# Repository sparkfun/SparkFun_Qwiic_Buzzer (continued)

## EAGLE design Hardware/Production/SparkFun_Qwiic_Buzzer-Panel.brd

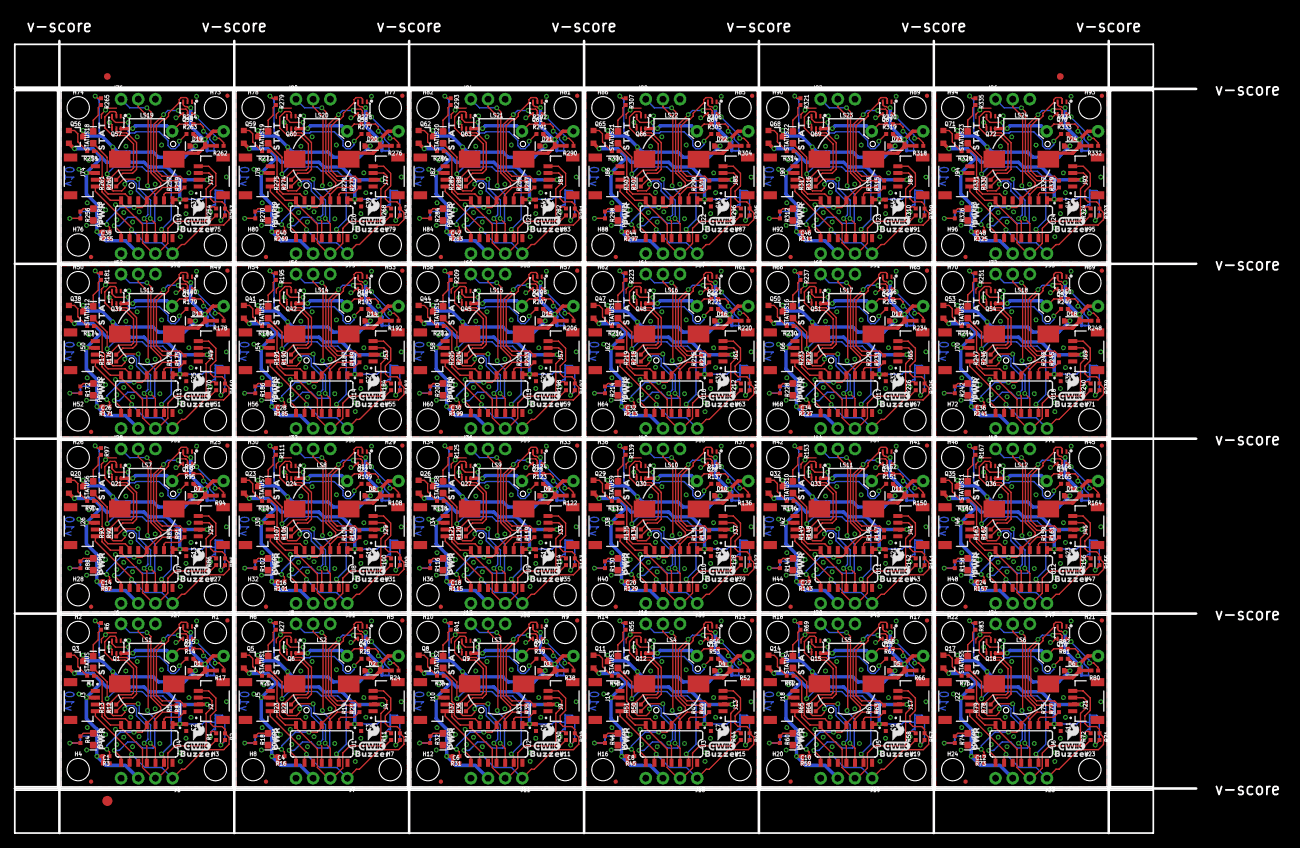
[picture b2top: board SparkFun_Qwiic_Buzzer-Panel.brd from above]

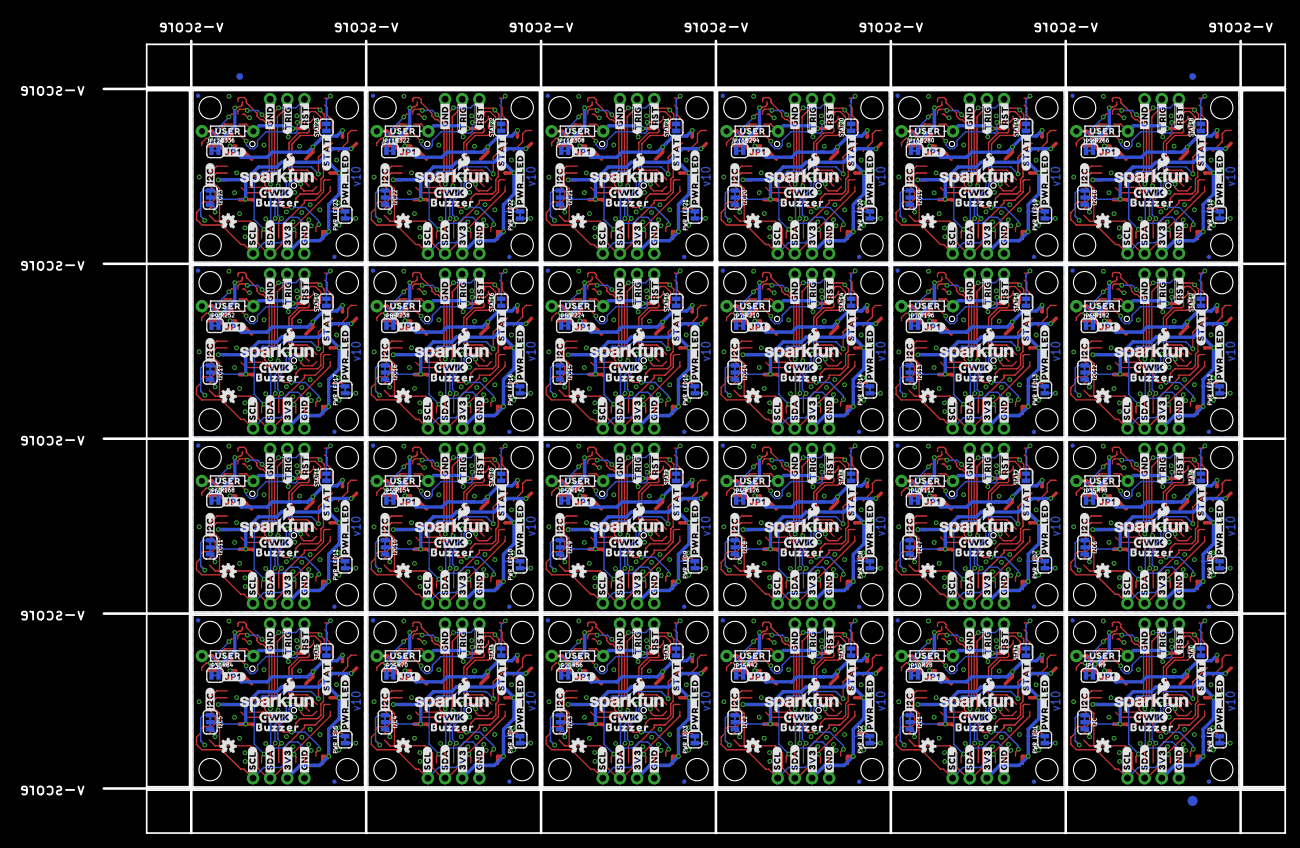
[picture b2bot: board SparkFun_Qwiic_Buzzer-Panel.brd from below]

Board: 2 copper layers, 175.0 x 117.3 mm, 1470 parts (555 on the bottom side), 696 nets.

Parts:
C1, C4, C6, C8, C10, C12, C14, C16, C18, C20, C22, C24, C26, C28, C30, C32, C34, C36, C38, C40, C42, C44, C46, C48: 10uF; 0402-TIGHT
C2, C3, C5, C7, C9, C11, C13, C15, C17, C19, C21, C23, C25, C27, C29, C31, C33, C35, C37, C39, C41, C43, C45, C47: 0.1uF; 0402-TIGHT
D1, D2, D3, D4, D5, D6, D7, D8, D9, D10, D11, D12, D13, D14, D15, D16, D17, D18, D19, D20, D21, D22, D23, D24: 0.5A/40V/420mV; SOD-323
E$1, E$2, E$3, E$4: FIDUCIAL-1X2
E$5, E$6: FIDUCIAL-1.5X3
H1, H2, H3, H4, H5, H6, H7, H8, H9, H10, H11, H12, H13, H14, H15, H16, H17, H18, H19, H20, H21, H22, H23, H24, H25, H26, H27, H28, H29, H30, H31, H32, H33, H34, H35, H36, H37, H38, H39, H40, H41, H42, H43, H44, H45, H46, H47, H48, H49, H50, H51, H52, H53, H54, H55, H56, H57, H58, H59, H60, H61, H62, H63, H64, H65, H66, H67, H68, H69, H70, H71, H72, H73, H74, H75, H76, H77, H78, H79, H80, H81, H82, H83, H84, H85, H86, H87, H88, H89, H90, H91, H92, H93, H94, H95, H96: STAND-OFF
I2C, I2C1, I2C2, I2C3, I2C4, I2C5, I2C6, I2C7, I2C8, I2C9, I2C10, I2C11, I2C12, I2C13, I2C14, I2C15, I2C16, I2C17, I2C18, I2C19, I2C20, I2C21, I2C22, I2C23: JUMPER-SMT_3_2-NC_TRACE_SILK; SMT-JUMPER_3_2-NC_TRACE_SILK
J1, J7, J11, J15, J19, J23, J27, J31, J35, J39, J43, J47, J51, J55, J59, J63, J67, J71, J75, J79, J83, J87, J91, J95: 1X04_NO_SILK
J2, J3, J4, J5, J9, J10, J13, J14, J17, J18, J21, J22, J25, J26, J29, J30, J33, J34, J37, J38, J41, J42, J45, J46, J49, J50, J53, J54, J57, J58, J61, J62, J65, J66, J69, J70, J73, J74, J77, J78, J81, J82, J85, J86, J89, J90, J93, J94: QWIIC_RA; JST04_1MM_RA
J6, J8, J12, J16, J20, J24, J28, J32, J36, J40, J44, J48, J52, J56, J60, J64, J68, J72, J76, J80, J84, J88, J92, J96: 1X03_NO_SILK
JP1, JP10, JP15, JP20, JP25, JP30, JP35, JP40, JP45, JP50, JP55, JP60, JP65, JP70, JP75, JP80, JP85, JP90, JP95, JP100, JP105, JP110, JP115, JP120: SMT-JUMPER_2_NC_TRACE_SILK
JP2, JP3, JP4, JP5, JP6, JP7, JP8, JP9, JP11, JP12, JP13, JP14, JP16, JP17, JP18, JP19, JP21, JP22, JP23, JP24, JP26, JP27, JP28, JP29, JP31, JP32, JP33, JP34, JP36, JP37, JP38, JP39, JP41, JP42, JP43, JP44, JP46, JP47, JP48, JP49, JP51, JP52, JP53, JP54, JP56, JP57, JP58, JP59, JP61, JP62, JP63, JP64, JP66, JP67, JP68, JP69, JP71, JP72, JP73, JP74, JP76, JP77, JP78, JP79, JP81, JP82, JP83, JP84, JP86, JP87, JP88, JP89, JP91, JP92, JP93, JP94, JP96, JP97, JP98, JP99, JP101, JP102, JP103, JP104, JP106, JP107, JP108, JP109, JP111, JP112, JP113, JP114, JP116, JP117, JP118, JP119: FIDUCIALUFIDUCIAL; FIDUCIAL-MICRO
LOGO1, LOGO3, LOGO9, LOGO13, LOGO17, LOGO21, LOGO25, LOGO29, LOGO33, LOGO37, LOGO41, LOGO45, LOGO49, LOGO53, LOGO57, LOGO61, LOGO65, LOGO69, LOGO73, LOGO77, LOGO81, LOGO85, LOGO89, LOGO93: OSHW-LOGOMINI; OSHW-LOGO-MINI
LOGO2, LOGO7, LOGO11, LOGO15, LOGO19, LOGO23, LOGO27, LOGO31, LOGO35, LOGO39, LOGO43, LOGO47, LOGO51, LOGO55, LOGO59, LOGO63, LOGO67, LOGO71, LOGO75, LOGO79, LOGO83, LOGO87, LOGO91, LOGO95: SFE_LOGO_NAME_FLAME.1_INCH; SFE_LOGO_NAME_FLAME_.1
LOGO4, LOGO6, LOGO10, LOGO14, LOGO18, LOGO22, LOGO26, LOGO30, LOGO34, LOGO38, LOGO42, LOGO46, LOGO50, LOGO54, LOGO58, LOGO62, LOGO66, LOGO70, LOGO74, LOGO78, LOGO82, LOGO86, LOGO90, LOGO94: SFE_LOGO_FLAME.1_INCH; SFE_LOGO_FLAME_.1
LOGO5, LOGO8, LOGO12, LOGO16, LOGO20, LOGO24, LOGO28, LOGO32, LOGO36, LOGO40, LOGO44, LOGO48, LOGO52, LOGO56, LOGO60, LOGO64, LOGO68, LOGO72, LOGO76, LOGO80, LOGO84, LOGO88, LOGO92, LOGO96: QWIIC_LOGO_4MM; QWIIC_4MM
LS1, LS2, LS3, LS4, LS5, LS6, LS7, LS8, LS9, LS10, LS11, LS12, LS13, LS14, LS15, LS16, LS17, LS18, LS19, LS20, LS21, LS22, LS23, LS24: BUZZER; BUZZER-CCV
POWER, POWER1, POWER2, POWER3, POWER4, POWER5, POWER6, POWER7, POWER8, POWER9, POWER10, POWER11, POWER12, POWER13, POWER14, POWER15, POWER16, POWER17, POWER18, POWER19, POWER20, POWER21, POWER22, POWER23: Red; LED-0603
PWR_LED, PWR_LED1, PWR_LED2, PWR_LED3, PWR_LED4, PWR_LED5, PWR_LED6, PWR_LED7, PWR_LED8, PWR_LED9, PWR_LED10, PWR_LED11, PWR_LED12, PWR_LED13, PWR_LED14, PWR_LED15, PWR_LED16, PWR_LED17, PWR_LED18, PWR_LED19, PWR_LED20, PWR_LED21, PWR_LED22, PWR_LED23: PWR_LED; SMT-JUMPER_2_NC_TRACE_SILK
Q1, Q2, Q4, Q6, Q7, Q9, Q10, Q12, Q13, Q15, Q16, Q18, Q19, Q21, Q22, Q24, Q25, Q27, Q28, Q30, Q31, Q33, Q34, Q36, Q37, Q39, Q40, Q42, Q43, Q45, Q46, Q48, Q49, Q51, Q52, Q54, Q55, Q57, Q58, Q60, Q61, Q63, Q64, Q66, Q67, Q69, Q70, Q72: SC70-6
Q3, Q5, Q8, Q11, Q14, Q17, Q20, Q23, Q26, Q29, Q32, Q35, Q38, Q41, Q44, Q47, Q50, Q53, Q56, Q59, Q62, Q65, Q68, Q71: 200mA/40V; SOT23-3
R1, R2, R6, R10, R11, R15, R26, R27, R29, R30, R40, R41, R43, R44, R54, R55, R57, R58, R68, R69, R71, R72, R82, R83, R85, R86, R96, R97, R99, R100, R110, R111, R113, R114, R124, R125, R127, R128, R138, R139, R141, R142, R152, R153, R155, R156, R166, R167, R169, R170, R180, R181, R183, R184, R194, R195, R197, R198, R208, R209, R211, R212, R222, R223, R225, R226, R236, R237, R239, R240, R250, R251, R253, R254, R264, R265, R267, R268, R278, R279, R281, R282, R292, R293, R295, R296, R306, R307, R309, R310, R320, R321, R323, R324, R334, R335: 2.2k; 0402-TIGHT
R3, R16, R31, R45, R59, R73, R87, R101, R115, R129, R143, R157, R171, R185, R199, R213, R227, R241, R255, R269, R283, R297, R311, R325: 10k; 0402-TIGHT
R4, R18, R32, R46, R60, R74, R88, R102, R116, R130, R144, R158, R172, R186, R200, R214, R228, R242, R256, R270, R284, R298, R312, R326: 4.7k; 0402-TIGHT
R5, R7, R8, R12, R13, R14, R19, R20, R21, R22, R23, R25, R33, R34, R35, R36, R37, R39, R47, R48, R49, R50, R51, R53, R61, R62, R63, R64, R65, R67, R75, R76, R77, R78, R79, R81, R89, R90, R91, R92, R93, R95, R103, R104, R105, R106, R107, R109, R117, R118, R119, R120, R121, R123, R131, R132, R133, R134, R135, R137, R145, R146, R147, R148, R149, R151, R159, R160, R161, R162, R163, R165, R173, R174, R175, R176, R177, R179, R187, R188, R189, R190, R191, R193, R201, R202, R203, R204, R205, R207, R215, R216, R217, R218, R219, R221, R229, R230, R231, R232, R233, R235, R243, R244, R245, R246, R247, R249, R257, R258, R259, R260, R261, R263, R271, R272, R273, R274, R275, R277, R285, R286, R287, R288, R289, R291, R299, R300, R301, R302, R303, R305, R313, R314, R315, R316, R317, R319, R327, R328, R329, R330, R331, R333: 330; 0402-TIGHT
R9, R28, R42, R56, R70, R84, R98, R112, R126, R140, R154, R168, R182, R196, R210, R224, R238, R252, R266, R280, R294, R308, R322, R336: USER; AXIAL-0.3
R17, R24, R38, R52, R66, R80, R94, R108, R122, R136, R150, R164, R178, R192, R206, R220, R234, R248, R262, R276, R290, R304, R318, R332: 100; 0402-TIGHT
STAT, STAT1, STAT2, STAT3, STAT4, STAT5, STAT6, STAT7, STAT8, STAT9, STAT10, STAT11, STAT12, STAT13, STAT14, STAT15, STAT16, STAT17, STAT18, STAT19, STAT20, STAT21, STAT22, STAT23: PWR_LED; SMT-JUMPER_2_NC_TRACE_SILK
STATUS, STATUS1, STATUS2, STATUS3, STATUS4, STATUS5, STATUS6, STATUS7, STATUS8, STATUS9, STATUS10, STATUS11, STATUS12, STATUS13, STATUS14, STATUS15, STATUS16, STATUS17, STATUS18, STATUS19, STATUS20, STATUS21, STATUS22, STATUS23: Blue; LED-0603
U1, U2, U3, U4, U5, U6, U7, U8, U9, U10, U11, U12, U13, U14, U15, U16, U17, U18, U19, U20, U21, U22, U23, U24: ATTINY84-ARDUINO; SO14
U$1, U$3, U$35, U$52, U$69, U$86, U$103, U$120, U$137, U$154, U$171, U$188, U$205, U$222, U$239, U$256, U$273, U$290, U$307, U$324, U$341, U$358, U$375, U$392: STAT0
U$2, U$10, U$23, U$24, U$40, U$41, U$57, U$58, U$74, U$75, U$91, U$92, U$108, U$109, U$125, U$126, U$142, U$143, U$159, U$160, U$176, U$177, U$193, U$194, U$210, U$211, U$227, U$228, U$244, U$245, U$261, U$262, U$278, U$279, U$295, U$296, U$312, U$313, U$329, U$330, U$346, U$347, U$363, U$364, U$380, U$381, U$397, U$398: #GND#0
U$4, U$9, U$36, U$53, U$70, U$87, U$104, U$121, U$138, U$155, U$172, U$189, U$206, U$223, U$240, U$257, U$274, U$291, U$308, U$325, U$342, U$359, U$376, U$393: PWR0
U$5, U$32, U$49, U$66, U$83, U$100, U$117, U$134, U$151, U$168, U$185, U$202, U$219, U$236, U$253, U$270, U$287, U$304, U$321, U$338, U$355, U$372, U$389, U$406: #PWR_LED#13
U$6, U$33, U$50, U$67, U$84, U$101, U$118, U$135, U$152, U$169, U$186, U$203, U$220, U$237, U$254, U$271, U$288, U$305, U$322, U$339, U$356, U$373, U$390, U$407: #JP1#14
U$7, U$28, U$45, U$62, U$79, U$96, U$113, U$130, U$147, U$164, U$181, U$198, U$215, U$232, U$249, U$266, U$283, U$300, U$317, U$334, U$351, U$368, U$385, U$402: #STAT#3
U$8, U$31, U$48, U$65, U$82, U$99, U$116, U$133, U$150, U$167, U$184, U$201, U$218, U$235, U$252, U$269, U$286, U$303, U$320, U$337, U$354, U$371, U$388, U$405: USER12
U$11, U$21, U$39, U$56, U$73, U$90, U$107, U$124, U$141, U$158, U$175, U$192, U$209, U$226, U$243, U$260, U$277, U$294, U$311, U$328, U$345, U$362, U$379, U$396: #I2C#0
U$12, U$29, U$46, U$63, U$80, U$97, U$114, U$131, U$148, U$165, U$182, U$199, U$216, U$233, U$250, U$267, U$284, U$301, U$318, U$335, U$352, U$369, U$386, U$403: ##RST##7
U$13, U$20, U$38, U$55, U$72, U$89, U$106, U$123, U$140, U$157, U$174, U$191, U$208, U$225, U$242, U$259, U$276, U$293, U$310, U$327, U$344, U$361, U$378, U$395: BUZZER1
U$14, U$16, U$37, U$54, U$71, U$88, U$105, U$122, U$139, U$156, U$173, U$190, U$207, U$224, U$241, U$258, U$275, U$292, U$309, U$326, U$343, U$360, U$377, U$394: QWIIC_5MM
U$15, U$30, U$47, U$64, U$81, U$98, U$115, U$132, U$149, U$166, U$183, U$200, U$217, U$234, U$251, U$268, U$285, U$302, U$319, U$336, U$353, U$370, U$387, U$404: ##TRIG##6
U$17, U$25, U$42, U$59, U$76, U$93, U$110, U$127, U$144, U$161, U$178, U$195, U$212, U$229, U$246, U$263, U$280, U$297, U$314, U$331, U$348, U$365, U$382, U$399: #3V3#0
U$18, U$27, U$44, U$61, U$78, U$95, U$112, U$129, U$146, U$163, U$180, U$197, U$214, U$231, U$248, U$265, U$282, U$299, U$316, U$333, U$350, U$367, U$384, U$401: #SCL#0
U$19, U$26, U$43, U$60, U$77, U$94, U$111, U$128, U$145, U$162, U$179, U$196, U$213, U$230, U$247, U$264, U$281, U$298, U$315, U$332, U$349, U$366, U$383, U$400: #SDA#0
U$22, U$34, U$51, U$68, U$85, U$102, U$119, U$136, U$153, U$170, U$187, U$204, U$221, U$238, U$255, U$272, U$289, U$306, U$323, U$340, U$357, U$374, U$391, U$408: BUZZER14

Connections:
3.3V: C1.1, C2.1, I2C.2, J1.3, J2.2, J3.2, PWR_LED.2, Q3.2, R3.2, U4.1
3.3V1: C3.1, C4.1, I2C1.2, J4.2, J5.2, J7.3, PWR_LED1.2, Q5.2, R16.2, U1.1
3.3V2: C5.1, C6.1, I2C2.2, J9.2, J10.2, J11.3, PWR_LED2.2, Q8.2, R31.2, U2.1
3.3V3: C7.1, C8.1, I2C3.2, J13.2, J14.2, J15.3, PWR_LED3.2, Q11.2, R45.2, U3.1
3.3V4: C9.1, C10.1, I2C4.2, J17.2, J18.2, J19.3, PWR_LED4.2, Q14.2, R59.2, U5.1
3.3V5: C11.1, C12.1, I2C5.2, J21.2, J22.2, J23.3, PWR_LED5.2, Q17.2, R73.2, U6.1
3.3V6: C13.1, C14.1, I2C6.2, J25.2, J26.2, J27.3, PWR_LED6.2, Q20.2, R87.2, U7.1
3.3V7: C15.1, C16.1, I2C7.2, J29.2, J30.2, J31.3, PWR_LED7.2, Q23.2, R101.2, U8.1
3.3V8: C17.1, C18.1, I2C8.2, J33.2, J34.2, J35.3, PWR_LED8.2, Q26.2, R115.2, U9.1
3.3V9: C19.1, C20.1, I2C9.2, J37.2, J38.2, J39.3, PWR_LED9.2, Q29.2, R129.2, U10.1
3.3V10: C21.1, C22.1, I2C10.2, J41.2, J42.2, J43.3, PWR_LED10.2, Q32.2, R143.2, U11.1
3.3V11: C23.1, C24.1, I2C11.2, J45.2, J46.2, J47.3, PWR_LED11.2, Q35.2, R157.2, U12.1
3.3V12: C25.1, C26.1, I2C12.2, J49.2, J50.2, J51.3, PWR_LED12.2, Q38.2, R171.2, U13.1
3.3V13: C27.1, C28.1, I2C13.2, J53.2, J54.2, J55.3, PWR_LED13.2, Q41.2, R185.2, U14.1
3.3V14: C29.1, C30.1, I2C14.2, J57.2, J58.2, J59.3, PWR_LED14.2, Q44.2, R199.2, U15.1
3.3V15: C31.1, C32.1, I2C15.2, J61.2, J62.2, J63.3, PWR_LED15.2, Q47.2, R213.2, U16.1
3.3V16: C33.1, C34.1, I2C16.2, J65.2, J66.2, J67.3, PWR_LED16.2, Q50.2, R227.2, U17.1
3.3V17: C35.1, C36.1, I2C17.2, J69.2, J70.2, J71.3, PWR_LED17.2, Q53.2, R241.2, U18.1
3.3V18: C37.1, C38.1, I2C18.2, J73.2, J74.2, J75.3, PWR_LED18.2, Q56.2, R255.2, U19.1
3.3V19: C39.1, C40.1, I2C19.2, J77.2, J78.2, J79.3, PWR_LED19.2, Q59.2, R269.2, U20.1
3.3V20: C41.1, C42.1, I2C20.2, J81.2, J82.2, J83.3, PWR_LED20.2, Q62.2, R283.2, U21.1
3.3V21: C43.1, C44.1, I2C21.2, J85.2, J86.2, J87.3, PWR_LED21.2, Q65.2, R297.2, U22.1
3.3V22: C45.1, C46.1, I2C22.2, J89.2, J90.2, J91.3, PWR_LED22.2, Q68.2, R311.2, U23.1
3.3V23: C47.1, C48.1, I2C23.2, J93.2, J94.2, J95.3, PWR_LED23.2, Q71.2, R325.2, U24.1
!RST: J6.1, R3.1, U4.4
!RST1: J8.1, R16.1, U1.4
!RST2: J12.1, R31.1, U2.4
!RST3: J16.1, R45.1, U3.4
!RST4: J20.1, R59.1, U5.4
!RST5: J24.1, R73.1, U6.4
!RST6: J28.1, R87.1, U7.4
!RST7: J32.1, R101.1, U8.4
!RST8: J36.1, R115.1, U9.4
!RST9: J40.1, R129.1, U10.4
!RST10: J44.1, R143.1, U11.4
!RST11: J48.1, R157.1, U12.4
!RST12: J52.1, R171.1, U13.4
!RST13: J56.1, R185.1, U14.4
!RST14: J60.1, R199.1, U15.4
!RST15: J64.1, R213.1, U16.4
!RST16: J68.1, R227.1, U17.4
!RST17: J72.1, R241.1, U18.4
!RST18: J76.1, R255.1, U19.4
!RST19: J80.1, R269.1, U20.4
!RST20: J84.1, R283.1, U21.4
!RST21: J88.1, R297.1, U22.4
!RST22: J92.1, R311.1, U23.4
!RST23: J96.1, R325.1, U24.4
!TRIGGER!: J6.2, U4.8
!TRIGGER!1: J8.2, U1.8
!TRIGGER!2: J12.2, U2.8
!TRIGGER!3: J16.2, U3.8
!TRIGGER!4: J20.2, U5.8
!TRIGGER!5: J24.2, U6.8
!TRIGGER!6: J28.2, U7.8
!TRIGGER!7: J32.2, U8.8
!TRIGGER!8: J36.2, U9.8
!TRIGGER!9: J40.2, U10.8
!TRIGGER!10: J44.2, U11.8
!TRIGGER!11: J48.2, U12.8
!TRIGGER!12: J52.2, U13.8
!TRIGGER!13: J56.2, U14.8
!TRIGGER!14: J60.2, U15.8
!TRIGGER!15: J64.2, U16.8
!TRIGGER!16: J68.2, U17.8
!TRIGGER!17: J72.2, U18.8
!TRIGGER!18: J76.2, U19.8
!TRIGGER!19: J80.2, U20.8
!TRIGGER!20: J84.2, U21.8
!TRIGGER!21: J88.2, U22.8
!TRIGGER!22: J92.2, U23.8
!TRIGGER!23: J96.2, U24.8
BUZZER: R7.1, U4.6
BUZZER1: R20.1, U1.6
BUZZER2: R34.1, U2.6
BUZZER3: R48.1, U3.6
BUZZER4: R62.1, U5.6
BUZZER5: R76.1, U6.6
BUZZER6: R90.1, U7.6
BUZZER7: R104.1, U8.6
BUZZER8: R118.1, U9.6
BUZZER9: R132.1, U10.6
BUZZER10: R146.1, U11.6
BUZZER11: R160.1, U12.6
BUZZER12: R174.1, U13.6
BUZZER13: R188.1, U14.6
BUZZER14: R202.1, U15.6
BUZZER15: R216.1, U16.6
BUZZER16: R230.1, U17.6
BUZZER17: R244.1, U18.6
BUZZER18: R258.1, U19.6
BUZZER19: R272.1, U20.6
BUZZER20: R286.1, U21.6
BUZZER21: R300.1, U22.6
BUZZER22: R314.1, U23.6
BUZZER23: R328.1, U24.6
GND: C1.2, C2.2, J1.4, J2.1, J3.1, J6.3, POWER.C, Q1.1, Q1.4, Q2.1, Q2.4, STAT.1, U4.14
GND1: C3.2, C4.2, J4.1, J5.1, J7.4, J8.3, POWER1.C, Q4.1, Q4.4, Q6.1, Q6.4, STAT1.1, U1.14
GND2: C5.2, C6.2, J9.1, J10.1, J11.4, J12.3, POWER2.C, Q7.1, Q7.4, Q9.1, Q9.4, STAT2.1, U2.14
GND3: C7.2, C8.2, J13.1, J14.1, J15.4, J16.3, POWER3.C, Q10.1, Q10.4, Q12.1, Q12.4, STAT3.1, U3.14
GND4: C9.2, C10.2, J17.1, J18.1, J19.4, J20.3, POWER4.C, Q13.1, Q13.4, Q15.1, Q15.4, STAT4.1, U5.14
GND5: C11.2, C12.2, J21.1, J22.1, J23.4, J24.3, POWER5.C, Q16.1, Q16.4, Q18.1, Q18.4, STAT5.1, U6.14
GND6: C13.2, C14.2, J25.1, J26.1, J27.4, J28.3, POWER6.C, Q19.1, Q19.4, Q21.1, Q21.4, STAT6.1, U7.14
GND7: C15.2, C16.2, J29.1, J30.1, J31.4, J32.3, POWER7.C, Q22.1, Q22.4, Q24.1, Q24.4, STAT7.1, U8.14
GND8: C17.2, C18.2, J33.1, J34.1, J35.4, J36.3, POWER8.C, Q25.1, Q25.4, Q27.1, Q27.4, STAT8.1, U9.14
GND9: C19.2, C20.2, J37.1, J38.1, J39.4, J40.3, POWER9.C, Q28.1, Q28.4, Q30.1, Q30.4, STAT9.1, U10.14
GND10: C21.2, C22.2, J41.1, J42.1, J43.4, J44.3, POWER10.C, Q31.1, Q31.4, Q33.1, Q33.4, STAT10.1, U11.14
GND11: C23.2, C24.2, J45.1, J46.1, J47.4, J48.3, POWER11.C, Q34.1, Q34.4, Q36.1, Q36.4, STAT11.1, U12.14
GND12: C25.2, C26.2, J49.1, J50.1, J51.4, J52.3, POWER12.C, Q37.1, Q37.4, Q39.1, Q39.4, STAT12.1, U13.14
GND13: C27.2, C28.2, J53.1, J54.1, J55.4, J56.3, POWER13.C, Q40.1, Q40.4, Q42.1, Q42.4, STAT13.1, U14.14
GND14: C29.2, C30.2, J57.1, J58.1, J59.4, J60.3, POWER14.C, Q43.1, Q43.4, Q45.1, Q45.4, STAT14.1, U15.14
GND15: C31.2, C32.2, J61.1, J62.1, J63.4, J64.3, POWER15.C, Q46.1, Q46.4, Q48.1, Q48.4, STAT15.1, U16.14
GND16: C33.2, C34.2, J65.1, J66.1, J67.4, J68.3, POWER16.C, Q49.1, Q49.4, Q51.1, Q51.4, STAT16.1, U17.14
GND17: C35.2, C36.2, J69.1, J70.1, J71.4, J72.3, POWER17.C, Q52.1, Q52.4, Q54.1, Q54.4, STAT17.1, U18.14
GND18: C37.2, C38.2, J73.1, J74.1, J75.4, J76.3, POWER18.C, Q55.1, Q55.4, Q57.1, Q57.4, STAT18.1, U19.14
GND19: C39.2, C40.2, J77.1, J78.1, J79.4, J80.3, POWER19.C, Q58.1, Q58.4, Q60.1, Q60.4, STAT19.1, U20.14
GND20: C41.2, C42.2, J81.1, J82.1, J83.4, J84.3, POWER20.C, Q61.1, Q61.4, Q63.1, Q63.4, STAT20.1, U21.14
GND21: C43.2, C44.2, J85.1, J86.1, J87.4, J88.3, POWER21.C, Q64.1, Q64.4, Q66.1, Q66.4, STAT21.1, U22.14
GND22: C45.2, C46.2, J89.1, J90.1, J91.4, J92.3, POWER22.C, Q67.1, Q67.4, Q69.1, Q69.4, STAT22.1, U23.14
GND23: C47.2, C48.2, J93.1, J94.1, J95.4, J96.3, POWER23.C, Q70.1, Q70.4, Q72.1, Q72.4, STAT23.1, U24.14
unnamed: PWR_LED.1, R4.2
unnamed: Q2.5, R5.2
unnamed: POWER.A, R4.1
unnamed: D1.A, JP1.2, LS1.-, Q2.3, R9.P$2, R14.2, R17.2
unnamed: Q3.1, R7.2
unnamed: D1.C, LS1.+, Q3.3
unnamed: R6.2, STATUS.C
unnamed: R6.1, STAT.2
unnamed: POWER1.A, R18.1
unnamed: Q1.2, R13.2
unnamed: Q1.5, R12.2
unnamed: Q2.2, R8.2
unnamed: Q2.6, R17.1
unnamed: Q1.3, R14.1
unnamed: Q1.6, R9.P$1, R15.1
unnamed: JP1.1, R15.2
unnamed: PWR_LED1.1, R18.2
unnamed: D2.A, JP10.2, LS2.-, Q4.3, R24.2, R25.2, R28.P$2
unnamed: Q5.1, R20.2
unnamed: Q4.5, R19.2
unnamed: D2.C, LS2.+, Q5.3
unnamed: Q6.2, R23.2
unnamed: Q6.5, R22.2
unnamed: Q4.2, R21.2
unnamed: Q4.6, R24.1
unnamed: Q6.3, R25.1
unnamed: Q6.6, R26.1, R28.P$1
unnamed: R27.2, STATUS1.C
unnamed: R27.1, STAT1.2
unnamed: JP10.1, R26.2
unnamed: POWER2.A, R32.1
unnamed: PWR_LED2.1, R32.2
unnamed: D3.A, JP15.2, LS3.-, Q7.3, R38.2, R39.2, R42.P$2
unnamed: Q8.1, R34.2
unnamed: Q7.5, R33.2
unnamed: D3.C, LS3.+, Q8.3
unnamed: Q9.2, R37.2
unnamed: Q9.5, R36.2
unnamed: Q7.2, R35.2
unnamed: Q7.6, R38.1
unnamed: Q9.3, R39.1
unnamed: Q9.6, R40.1, R42.P$1
unnamed: R41.2, STATUS2.C
unnamed: R41.1, STAT2.2
unnamed: JP15.1, R40.2
unnamed: POWER3.A, R46.1
unnamed: PWR_LED3.1, R46.2
unnamed: D4.A, JP20.2, LS4.-, Q10.3, R52.2, R53.2, R56.P$2
unnamed: Q11.1, R48.2
unnamed: Q10.5, R47.2
unnamed: D4.C, LS4.+, Q11.3
unnamed: Q12.2, R51.2
unnamed: Q12.5, R50.2
unnamed: Q10.2, R49.2
unnamed: Q10.6, R52.1
unnamed: Q12.3, R53.1
unnamed: Q12.6, R54.1, R56.P$1
unnamed: R55.2, STATUS3.C
unnamed: R55.1, STAT3.2
unnamed: JP20.1, R54.2
unnamed: POWER4.A, R60.1
unnamed: PWR_LED4.1, R60.2
unnamed: D5.A, JP25.2, LS5.-, Q13.3, R66.2, R67.2, R70.P$2
unnamed: Q14.1, R62.2
unnamed: Q13.5, R61.2
unnamed: D5.C, LS5.+, Q14.3
unnamed: Q15.2, R65.2
unnamed: Q15.5, R64.2
unnamed: Q13.2, R63.2
unnamed: Q13.6, R66.1
unnamed: Q15.3, R67.1
unnamed: Q15.6, R68.1, R70.P$1
unnamed: R69.2, STATUS4.C
unnamed: R69.1, STAT4.2
unnamed: JP25.1, R68.2
unnamed: POWER5.A, R74.1
unnamed: PWR_LED5.1, R74.2
unnamed: D6.A, JP30.2, LS6.-, Q16.3, R80.2, R81.2, R84.P$2
unnamed: Q17.1, R76.2
unnamed: Q16.5, R75.2
unnamed: D6.C, LS6.+, Q17.3
unnamed: Q18.2, R79.2
unnamed: Q18.5, R78.2
unnamed: Q16.2, R77.2
unnamed: Q16.6, R80.1
unnamed: Q18.3, R81.1
unnamed: Q18.6, R82.1, R84.P$1
unnamed: R83.2, STATUS5.C
unnamed: R83.1, STAT5.2
unnamed: JP30.1, R82.2
unnamed: POWER6.A, R88.1
unnamed: PWR_LED6.1, R88.2
unnamed: D7.A, JP35.2, LS7.-, Q19.3, R94.2, R95.2, R98.P$2
unnamed: Q20.1, R90.2
unnamed: Q19.5, R89.2
unnamed: D7.C, LS7.+, Q20.3
unnamed: Q21.2, R93.2
unnamed: Q21.5, R92.2
unnamed: Q19.2, R91.2
unnamed: Q19.6, R94.1
unnamed: Q21.3, R95.1
unnamed: Q21.6, R96.1, R98.P$1
unnamed: R97.2, STATUS6.C
unnamed: R97.1, STAT6.2
unnamed: JP35.1, R96.2
unnamed: POWER7.A, R102.1
unnamed: PWR_LED7.1, R102.2
unnamed: D8.A, JP40.2, LS8.-, Q22.3, R108.2, R109.2, R112.P$2
unnamed: Q23.1, R104.2
unnamed: Q22.5, R103.2
unnamed: D8.C, LS8.+, Q23.3
unnamed: Q24.2, R107.2
unnamed: Q24.5, R106.2
unnamed: Q22.2, R105.2
unnamed: Q22.6, R108.1
unnamed: Q24.3, R109.1
unnamed: Q24.6, R110.1, R112.P$1
unnamed: R111.2, STATUS7.C
unnamed: R111.1, STAT7.2
unnamed: JP40.1, R110.2
unnamed: POWER8.A, R116.1
unnamed: PWR_LED8.1, R116.2
unnamed: D9.A, JP45.2, LS9.-, Q25.3, R122.2, R123.2, R126.P$2
unnamed: Q26.1, R118.2
unnamed: Q25.5, R117.2
unnamed: D9.C, LS9.+, Q26.3
unnamed: Q27.2, R121.2
unnamed: Q27.5, R120.2
unnamed: Q25.2, R119.2
unnamed: Q25.6, R122.1
unnamed: Q27.3, R123.1
unnamed: Q27.6, R124.1, R126.P$1
unnamed: R125.2, STATUS8.C
unnamed: R125.1, STAT8.2
unnamed: JP45.1, R124.2
unnamed: POWER9.A, R130.1
unnamed: PWR_LED9.1, R130.2
unnamed: D10.A, JP50.2, LS10.-, Q28.3, R136.2, R137.2, R140.P$2
unnamed: Q29.1, R132.2
unnamed: Q28.5, R131.2
unnamed: D10.C, LS10.+, Q29.3
unnamed: Q30.2, R135.2
unnamed: Q30.5, R134.2
unnamed: Q28.2, R133.2
unnamed: Q28.6, R136.1
unnamed: Q30.3, R137.1
unnamed: Q30.6, R138.1, R140.P$1
unnamed: R139.2, STATUS9.C
unnamed: R139.1, STAT9.2
unnamed: JP50.1, R138.2
unnamed: POWER10.A, R144.1
unnamed: PWR_LED10.1, R144.2
unnamed: D11.A, JP55.2, LS11.-, Q31.3, R150.2, R151.2, R154.P$2
unnamed: Q32.1, R146.2
unnamed: Q31.5, R145.2
unnamed: D11.C, LS11.+, Q32.3
unnamed: Q33.2, R149.2
unnamed: Q33.5, R148.2
unnamed: Q31.2, R147.2
unnamed: Q31.6, R150.1
unnamed: Q33.3, R151.1
unnamed: Q33.6, R152.1, R154.P$1
unnamed: R153.2, STATUS10.C
unnamed: R153.1, STAT10.2
unnamed: JP55.1, R152.2
unnamed: POWER11.A, R158.1
unnamed: PWR_LED11.1, R158.2
unnamed: D12.A, JP60.2, LS12.-, Q34.3, R164.2, R165.2, R168.P$2
unnamed: Q35.1, R160.2
unnamed: Q34.5, R159.2
unnamed: D12.C, LS12.+, Q35.3
unnamed: Q36.2, R163.2
unnamed: Q36.5, R162.2
unnamed: Q34.2, R161.2
unnamed: Q34.6, R164.1
unnamed: Q36.3, R165.1
unnamed: Q36.6, R166.1, R168.P$1
unnamed: R167.2, STATUS11.C
unnamed: R167.1, STAT11.2
unnamed: JP60.1, R166.2
unnamed: POWER12.A, R172.1
unnamed: PWR_LED12.1, R172.2
unnamed: D13.A, JP65.2, LS13.-, Q37.3, R178.2, R179.2, R182.P$2
unnamed: Q38.1, R174.2
unnamed: Q37.5, R173.2
unnamed: D13.C, LS13.+, Q38.3
unnamed: Q39.2, R177.2
unnamed: Q39.5, R176.2
unnamed: Q37.2, R175.2
unnamed: Q37.6, R178.1
unnamed: Q39.3, R179.1
unnamed: Q39.6, R180.1, R182.P$1
unnamed: R181.2, STATUS12.C
unnamed: R181.1, STAT12.2
unnamed: JP65.1, R180.2
unnamed: POWER13.A, R186.1
unnamed: PWR_LED13.1, R186.2
unnamed: D14.A, JP70.2, LS14.-, Q40.3, R192.2, R193.2, R196.P$2
unnamed: Q41.1, R188.2
unnamed: Q40.5, R187.2
unnamed: D14.C, LS14.+, Q41.3
unnamed: Q42.2, R191.2
unnamed: Q42.5, R190.2
unnamed: Q40.2, R189.2
unnamed: Q40.6, R192.1
unnamed: Q42.3, R193.1
unnamed: Q42.6, R194.1, R196.P$1
unnamed: R195.2, STATUS13.C
unnamed: R195.1, STAT13.2
unnamed: JP70.1, R194.2
unnamed: POWER14.A, R200.1
unnamed: PWR_LED14.1, R200.2
unnamed: D15.A, JP75.2, LS15.-, Q43.3, R206.2, R207.2, R210.P$2
unnamed: Q44.1, R202.2
unnamed: Q43.5, R201.2
unnamed: D15.C, LS15.+, Q44.3
unnamed: Q45.2, R205.2
unnamed: Q45.5, R204.2
unnamed: Q43.2, R203.2
unnamed: Q43.6, R206.1
unnamed: Q45.3, R207.1
unnamed: Q45.6, R208.1, R210.P$1
unnamed: R209.2, STATUS14.C
unnamed: R209.1, STAT14.2
unnamed: JP75.1, R208.2
unnamed: POWER15.A, R214.1
unnamed: PWR_LED15.1, R214.2
unnamed: D16.A, JP80.2, LS16.-, Q46.3, R220.2, R221.2, R224.P$2
unnamed: Q47.1, R216.2
unnamed: Q46.5, R215.2
unnamed: D16.C, LS16.+, Q47.3
unnamed: Q48.2, R219.2
unnamed: Q48.5, R218.2
unnamed: Q46.2, R217.2
unnamed: Q46.6, R220.1
unnamed: Q48.3, R221.1
unnamed: Q48.6, R222.1, R224.P$1
unnamed: R223.2, STATUS15.C
unnamed: R223.1, STAT15.2
unnamed: JP80.1, R222.2
unnamed: POWER16.A, R228.1
unnamed: PWR_LED16.1, R228.2
unnamed: D17.A, JP85.2, LS17.-, Q49.3, R234.2, R235.2, R238.P$2
unnamed: Q50.1, R230.2
unnamed: Q49.5, R229.2
unnamed: D17.C, LS17.+, Q50.3
unnamed: Q51.2, R233.2
unnamed: Q51.5, R232.2
unnamed: Q49.2, R231.2
unnamed: Q49.6, R234.1
unnamed: Q51.3, R235.1
unnamed: Q51.6, R236.1, R238.P$1
unnamed: R237.2, STATUS16.C
unnamed: R237.1, STAT16.2
unnamed: JP85.1, R236.2
unnamed: POWER17.A, R242.1
unnamed: PWR_LED17.1, R242.2
unnamed: D18.A, JP90.2, LS18.-, Q52.3, R248.2, R249.2, R252.P$2
unnamed: Q53.1, R244.2
unnamed: Q52.5, R243.2
unnamed: D18.C, LS18.+, Q53.3
unnamed: Q54.2, R247.2
unnamed: Q54.5, R246.2
unnamed: Q52.2, R245.2
unnamed: Q52.6, R248.1
unnamed: Q54.3, R249.1
unnamed: Q54.6, R250.1, R252.P$1
unnamed: R251.2, STATUS17.C
unnamed: R251.1, STAT17.2
unnamed: JP90.1, R250.2
unnamed: POWER18.A, R256.1
unnamed: PWR_LED18.1, R256.2
unnamed: D19.A, JP95.2, LS19.-, Q55.3, R262.2, R263.2, R266.P$2
unnamed: Q56.1, R258.2
unnamed: Q55.5, R257.2
unnamed: D19.C, LS19.+, Q56.3
unnamed: Q57.2, R261.2
unnamed: Q57.5, R260.2
unnamed: Q55.2, R259.2
unnamed: Q55.6, R262.1
unnamed: Q57.3, R263.1
unnamed: Q57.6, R264.1, R266.P$1
unnamed: R265.2, STATUS18.C
unnamed: R265.1, STAT18.2
unnamed: JP95.1, R264.2
unnamed: POWER19.A, R270.1
unnamed: PWR_LED19.1, R270.2
unnamed: D20.A, JP100.2, LS20.-, Q58.3, R276.2, R277.2, R280.P$2
unnamed: Q59.1, R272.2
unnamed: Q58.5, R271.2
unnamed: D20.C, LS20.+, Q59.3
unnamed: Q60.2, R275.2
unnamed: Q60.5, R274.2
unnamed: Q58.2, R273.2
unnamed: Q58.6, R276.1
unnamed: Q60.3, R277.1
unnamed: Q60.6, R278.1, R280.P$1
unnamed: R279.2, STATUS19.C
unnamed: R279.1, STAT19.2
unnamed: JP100.1, R278.2
unnamed: POWER20.A, R284.1
unnamed: PWR_LED20.1, R284.2
unnamed: D21.A, JP105.2, LS21.-, Q61.3, R290.2, R291.2, R294.P$2
unnamed: Q62.1, R286.2
unnamed: Q61.5, R285.2
unnamed: D21.C, LS21.+, Q62.3
unnamed: Q63.2, R289.2
unnamed: Q63.5, R288.2
unnamed: Q61.2, R287.2
unnamed: Q61.6, R290.1
unnamed: Q63.3, R291.1
unnamed: Q63.6, R292.1, R294.P$1
unnamed: R293.2, STATUS20.C
unnamed: R293.1, STAT20.2
unnamed: JP105.1, R292.2
unnamed: POWER21.A, R298.1
unnamed: PWR_LED21.1, R298.2
unnamed: D22.A, JP110.2, LS22.-, Q64.3, R304.2, R305.2, R308.P$2
unnamed: Q65.1, R300.2
unnamed: Q64.5, R299.2
unnamed: D22.C, LS22.+, Q65.3
unnamed: Q66.2, R303.2
unnamed: Q66.5, R302.2
unnamed: Q64.2, R301.2
unnamed: Q64.6, R304.1
unnamed: Q66.3, R305.1
unnamed: Q66.6, R306.1, R308.P$1
unnamed: R307.2, STATUS21.C
unnamed: R307.1, STAT21.2
unnamed: JP110.1, R306.2
unnamed: POWER22.A, R312.1
unnamed: PWR_LED22.1, R312.2
unnamed: D23.A, JP115.2, LS23.-, Q67.3, R318.2, R319.2, R322.P$2
unnamed: Q68.1, R314.2
unnamed: Q67.5, R313.2
unnamed: D23.C, LS23.+, Q68.3
unnamed: Q69.2, R317.2
unnamed: Q69.5, R316.2
unnamed: Q67.2, R315.2
unnamed: Q67.6, R318.1
unnamed: Q69.3, R319.1
unnamed: Q69.6, R320.1, R322.P$1
unnamed: R321.2, STATUS22.C
unnamed: R321.1, STAT22.2
unnamed: JP115.1, R320.2
unnamed: POWER23.A, R326.1
unnamed: PWR_LED23.1, R326.2
unnamed: D24.A, JP120.2, LS24.-, Q70.3, R332.2, R333.2, R336.P$2
unnamed: Q71.1, R328.2
unnamed: Q70.5, R327.2
unnamed: D24.C, LS24.+, Q71.3
unnamed: Q72.2, R331.2
unnamed: Q72.5, R330.2
unnamed: Q70.2, R329.2
unnamed: Q70.6, R332.1
unnamed: Q72.3, R333.1
unnamed: Q72.6, R334.1, R336.P$1
unnamed: R335.2, STATUS23.C
unnamed: R335.1, STAT23.2
unnamed: JP120.1, R334.2
SCL: J1.1, J2.4, J3.4, R2.1, U4.9
SCL1: J4.4, J5.4, J7.1, R10.1, U1.9
SCL2: J9.4, J10.4, J11.1, R29.1, U2.9
SCL3: J13.4, J14.4, J15.1, R43.1, U3.9
SCL4: J17.4, J18.4, J19.1, R57.1, U5.9
SCL5: J21.4, J22.4, J23.1, R71.1, U6.9
SCL6: J25.4, J26.4, J27.1, R85.1, U7.9
SCL7: J29.4, J30.4, J31.1, R99.1, U8.9
SCL8: J33.4, J34.4, J35.1, R113.1, U9.9
SCL9: J37.4, J38.4, J39.1, R127.1, U10.9
SCL10: J41.4, J42.4, J43.1, R141.1, U11.9
SCL11: J45.4, J46.4, J47.1, R155.1, U12.9
SCL12: J49.4, J50.4, J51.1, R169.1, U13.9
SCL13: J53.4, J54.4, J55.1, R183.1, U14.9
SCL14: J57.4, J58.4, J59.1, R197.1, U15.9
SCL15: J61.4, J62.4, J63.1, R211.1, U16.9
SCL16: J65.4, J66.4, J67.1, R225.1, U17.9
SCL17: J69.4, J70.4, J71.1, R239.1, U18.9
SCL18: J73.4, J74.4, J75.1, R253.1, U19.9
SCL19: J77.4, J78.4, J79.1, R267.1, U20.9
SCL20: J81.4, J82.4, J83.1, R281.1, U21.9
SCL21: J85.4, J86.4, J87.1, R295.1, U22.9
SCL22: J89.4, J90.4, J91.1, R309.1, U23.9
SCL23: J93.4, J94.4, J95.1, R323.1, U24.9
SCL_PU1: I2C.1, R2.2
SCL_PU2: I2C1.1, R10.2
SCL_PU3: I2C2.1, R29.2
SCL_PU4: I2C3.1, R43.2
SCL_PU5: I2C4.1, R57.2
SCL_PU6: I2C5.1, R71.2
SCL_PU7: I2C6.1, R85.2
SCL_PU8: I2C7.1, R99.2
SCL_PU9: I2C8.1, R113.2
SCL_PU10: I2C9.1, R127.2
SCL_PU11: I2C10.1, R141.2
SCL_PU12: I2C11.1, R155.2
SCL_PU13: I2C12.1, R169.2
SCL_PU14: I2C13.1, R183.2
SCL_PU15: I2C14.1, R197.2
SCL_PU16: I2C15.1, R211.2
SCL_PU17: I2C16.1, R225.2
SCL_PU18: I2C17.1, R239.2
SCL_PU19: I2C18.1, R253.2
SCL_PU20: I2C19.1, R267.2
SCL_PU21: I2C20.1, R281.2
SCL_PU22: I2C21.1, R295.2
SCL_PU23: I2C22.1, R309.2
SCL_PU24: I2C23.1, R323.2
SDA: J1.2, J2.3, J3.3, R1.1, U4.7
SDA1: J4.3, J5.3, J7.2, R11.1, U1.7
SDA2: J9.3, J10.3, J11.2, R30.1, U2.7
SDA3: J13.3, J14.3, J15.2, R44.1, U3.7
SDA4: J17.3, J18.3, J19.2, R58.1, U5.7
SDA5: J21.3, J22.3, J23.2, R72.1, U6.7
SDA6: J25.3, J26.3, J27.2, R86.1, U7.7
SDA7: J29.3, J30.3, J31.2, R100.1, U8.7
SDA8: J33.3, J34.3, J35.2, R114.1, U9.7
SDA9: J37.3, J38.3, J39.2, R128.1, U10.7
SDA10: J41.3, J42.3, J43.2, R142.1, U11.7
SDA11: J45.3, J46.3, J47.2, R156.1, U12.7
SDA12: J49.3, J50.3, J51.2, R170.1, U13.7
SDA13: J53.3, J54.3, J55.2, R184.1, U14.7
SDA14: J57.3, J58.3, J59.2, R198.1, U15.7
SDA15: J61.3, J62.3, J63.2, R212.1, U16.7
SDA16: J65.3, J66.3, J67.2, R226.1, U17.7
SDA17: J69.3, J70.3, J71.2, R240.1, U18.7
SDA18: J73.3, J74.3, J75.2, R254.1, U19.7
SDA19: J77.3, J78.3, J79.2, R268.1, U20.7
SDA20: J81.3, J82.3, J83.2, R282.1, U21.7
SDA21: J85.3, J86.3, J87.2, R296.1, U22.7
SDA22: J89.3, J90.3, J91.2, R310.1, U23.7
SDA23: J93.3, J94.3, J95.2, R324.1, U24.7
SDA_PU1: I2C.3, R1.2
SDA_PU2: I2C1.3, R11.2
SDA_PU3: I2C2.3, R30.2
SDA_PU4: I2C3.3, R44.2
SDA_PU5: I2C4.3, R58.2
SDA_PU6: I2C5.3, R72.2
SDA_PU7: I2C6.3, R86.2
SDA_PU8: I2C7.3, R100.2
SDA_PU9: I2C8.3, R114.2
SDA_PU10: I2C9.3, R128.2
SDA_PU11: I2C10.3, R142.2
SDA_PU12: I2C11.3, R156.2
SDA_PU13: I2C12.3, R170.2
SDA_PU14: I2C13.3, R184.2
SDA_PU15: I2C14.3, R198.2
SDA_PU16: I2C15.3, R212.2
SDA_PU17: I2C16.3, R226.2
SDA_PU18: I2C17.3, R240.2
SDA_PU19: I2C18.3, R254.2
SDA_PU20: I2C19.3, R268.2
SDA_PU21: I2C20.3, R282.2
SDA_PU22: I2C21.3, R296.2
SDA_PU23: I2C22.3, R310.2
SDA_PU24: I2C23.3, R324.2
STAT: STATUS.A, U4.13
STAT1: STATUS1.A, U1.13
STAT2: STATUS2.A, U2.13
STAT3: STATUS3.A, U3.13
STAT4: STATUS4.A, U5.13
STAT5: STATUS5.A, U6.13
STAT6: STATUS6.A, U7.13
STAT7: STATUS7.A, U8.13
STAT8: STATUS8.A, U9.13
STAT9: STATUS9.A, U10.13
STAT10: STATUS10.A, U11.13
STAT11: STATUS11.A, U12.13
STAT12: STATUS12.A, U13.13
STAT13: STATUS13.A, U14.13
STAT14: STATUS14.A, U15.13
STAT15: STATUS15.A, U16.13
STAT16: STATUS16.A, U17.13
STAT17: STATUS17.A, U18.13
STAT18: STATUS18.A, U19.13
STAT19: STATUS19.A, U20.13
STAT20: STATUS20.A, U21.13
STAT21: STATUS21.A, U22.13
STAT22: STATUS22.A, U23.13
STAT23: STATUS23.A, U24.13
VOL_0: R5.1, U4.3
VOL_1: R8.1, U4.2
VOL_2: R12.1, U4.12
VOL_3: R13.1, U4.11
VOL_4: R19.1, U1.3
VOL_5: R21.1, U1.2
VOL_6: R22.1, U1.12
VOL_7: R23.1, U1.11
VOL_8: R33.1, U2.3
VOL_9: R35.1, U2.2
VOL_10: R36.1, U2.12
VOL_11: R37.1, U2.11
VOL_12: R47.1, U3.3
VOL_13: R49.1, U3.2
VOL_14: R50.1, U3.12
VOL_15: R51.1, U3.11
VOL_16: R61.1, U5.3
VOL_17: R63.1, U5.2
VOL_18: R64.1, U5.12
VOL_19: R65.1, U5.11
VOL_20: R75.1, U6.3
VOL_21: R77.1, U6.2
VOL_22: R78.1, U6.12
VOL_23: R79.1, U6.11
VOL_24: R89.1, U7.3
VOL_25: R91.1, U7.2
VOL_26: R92.1, U7.12
VOL_27: R93.1, U7.11
VOL_28: R103.1, U8.3
VOL_29: R105.1, U8.2
VOL_30: R106.1, U8.12
VOL_31: R107.1, U8.11
VOL_32: R117.1, U9.3
VOL_33: R119.1, U9.2
VOL_34: R120.1, U9.12
VOL_35: R121.1, U9.11
VOL_36: R131.1, U10.3
VOL_37: R133.1, U10.2
VOL_38: R134.1, U10.12
VOL_39: R135.1, U10.11
VOL_40: R145.1, U11.3
VOL_41: R147.1, U11.2
VOL_42: R148.1, U11.12
VOL_43: R149.1, U11.11
VOL_44: R159.1, U12.3
VOL_45: R161.1, U12.2
VOL_46: R162.1, U12.12
VOL_47: R163.1, U12.11
VOL_48: R173.1, U13.3
VOL_49: R175.1, U13.2
VOL_50: R176.1, U13.12
VOL_51: R177.1, U13.11
VOL_52: R187.1, U14.3
VOL_53: R189.1, U14.2
VOL_54: R190.1, U14.12
VOL_55: R191.1, U14.11
VOL_56: R201.1, U15.3
VOL_57: R203.1, U15.2
VOL_58: R204.1, U15.12
VOL_59: R205.1, U15.11
VOL_60: R215.1, U16.3
VOL_61: R217.1, U16.2
VOL_62: R218.1, U16.12
VOL_63: R219.1, U16.11
VOL_64: R229.1, U17.3
VOL_65: R231.1, U17.2
VOL_66: R232.1, U17.12
VOL_67: R233.1, U17.11
VOL_68: R243.1, U18.3
VOL_69: R245.1, U18.2
VOL_70: R246.1, U18.12
VOL_71: R247.1, U18.11
VOL_72: R257.1, U19.3
VOL_73: R259.1, U19.2
VOL_74: R260.1, U19.12
VOL_75: R261.1, U19.11
VOL_76: R271.1, U20.3
VOL_77: R273.1, U20.2
VOL_78: R274.1, U20.12
VOL_79: R275.1, U20.11
VOL_80: R285.1, U21.3
VOL_81: R287.1, U21.2
VOL_82: R288.1, U21.12
VOL_83: R289.1, U21.11
VOL_84: R299.1, U22.3
VOL_85: R301.1, U22.2
VOL_86: R302.1, U22.12
VOL_87: R303.1, U22.11
VOL_88: R313.1, U23.3
VOL_89: R315.1, U23.2
VOL_90: R316.1, U23.12
VOL_91: R317.1, U23.11
VOL_92: R327.1, U24.3
VOL_93: R329.1, U24.2
VOL_94: R330.1, U24.12
VOL_95: R331.1, U24.11
